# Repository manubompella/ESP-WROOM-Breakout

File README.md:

# ESP-WROOM-Breakout
Breakouts for ESP8266 and ESP32 WiFi/WLAN + Bluetooth modules from Espressif.
*Note: AI-Thinker ESP-13 is compatible with Espressif ESP-WROOM-02 and AI-Thinker ESP-32S is compatible with Espressif ESP-WROOM-32.*

## Shop
* [ESP-WROOM-02-Breakout (ESP8266)](http://www.watterott.com/en/ESP-WROOM02-Breakout)
* [ESP-WROOM-32-Breakout (ESP32)](http://www.watterott.com/en/ESP-WROOM32-Breakout)

## Features
* Espressif [ESP8266 ESP-WROOM-02](http://espressif.com/en/products/hardware/esp8266ex/overview) WiFi module
* Espressif [ESP32 ESP-WROOM-32](http://espressif.com/en/products/hardware/esp32/overview) WiFi+Bluetooth module
* WiFi standard: IEEE 802.11b/g/n 2.4GHz
* WiFi security: WEP, WPA, WPA2, WAPI
* WiFi Direct and Soft-AP (Access-Point mode)
* Classic and BLE Bluetooth (ESP32)
* Silabs [CP2102N](http://www.silabs.com/products/interface/usb-bridges/usbxpress-usb-bridges/Pages/usbxpress-usb-bridges.aspx) USB UART Bridge (up to 3M baud)
* microUSB-Connector

## Hardware and Software
* [Schematics + Layout](https://github.com/watterott/ESP-WROOM-Breakout/tree/master/hardware)
* ESP8266: [Arduino Core](https://github.com/esp8266/Arduino) (Board: NodeMCU v1)
* ESP32: [Arduino Core](https://github.com/espressif/arduino-esp32) (Board: ESP32 Dev Module)
* [Silabs Serial Port Driver (VCP)](http://www.silabs.com/products/mcu/pages/usbtouartbridgevcpdrivers.aspx)

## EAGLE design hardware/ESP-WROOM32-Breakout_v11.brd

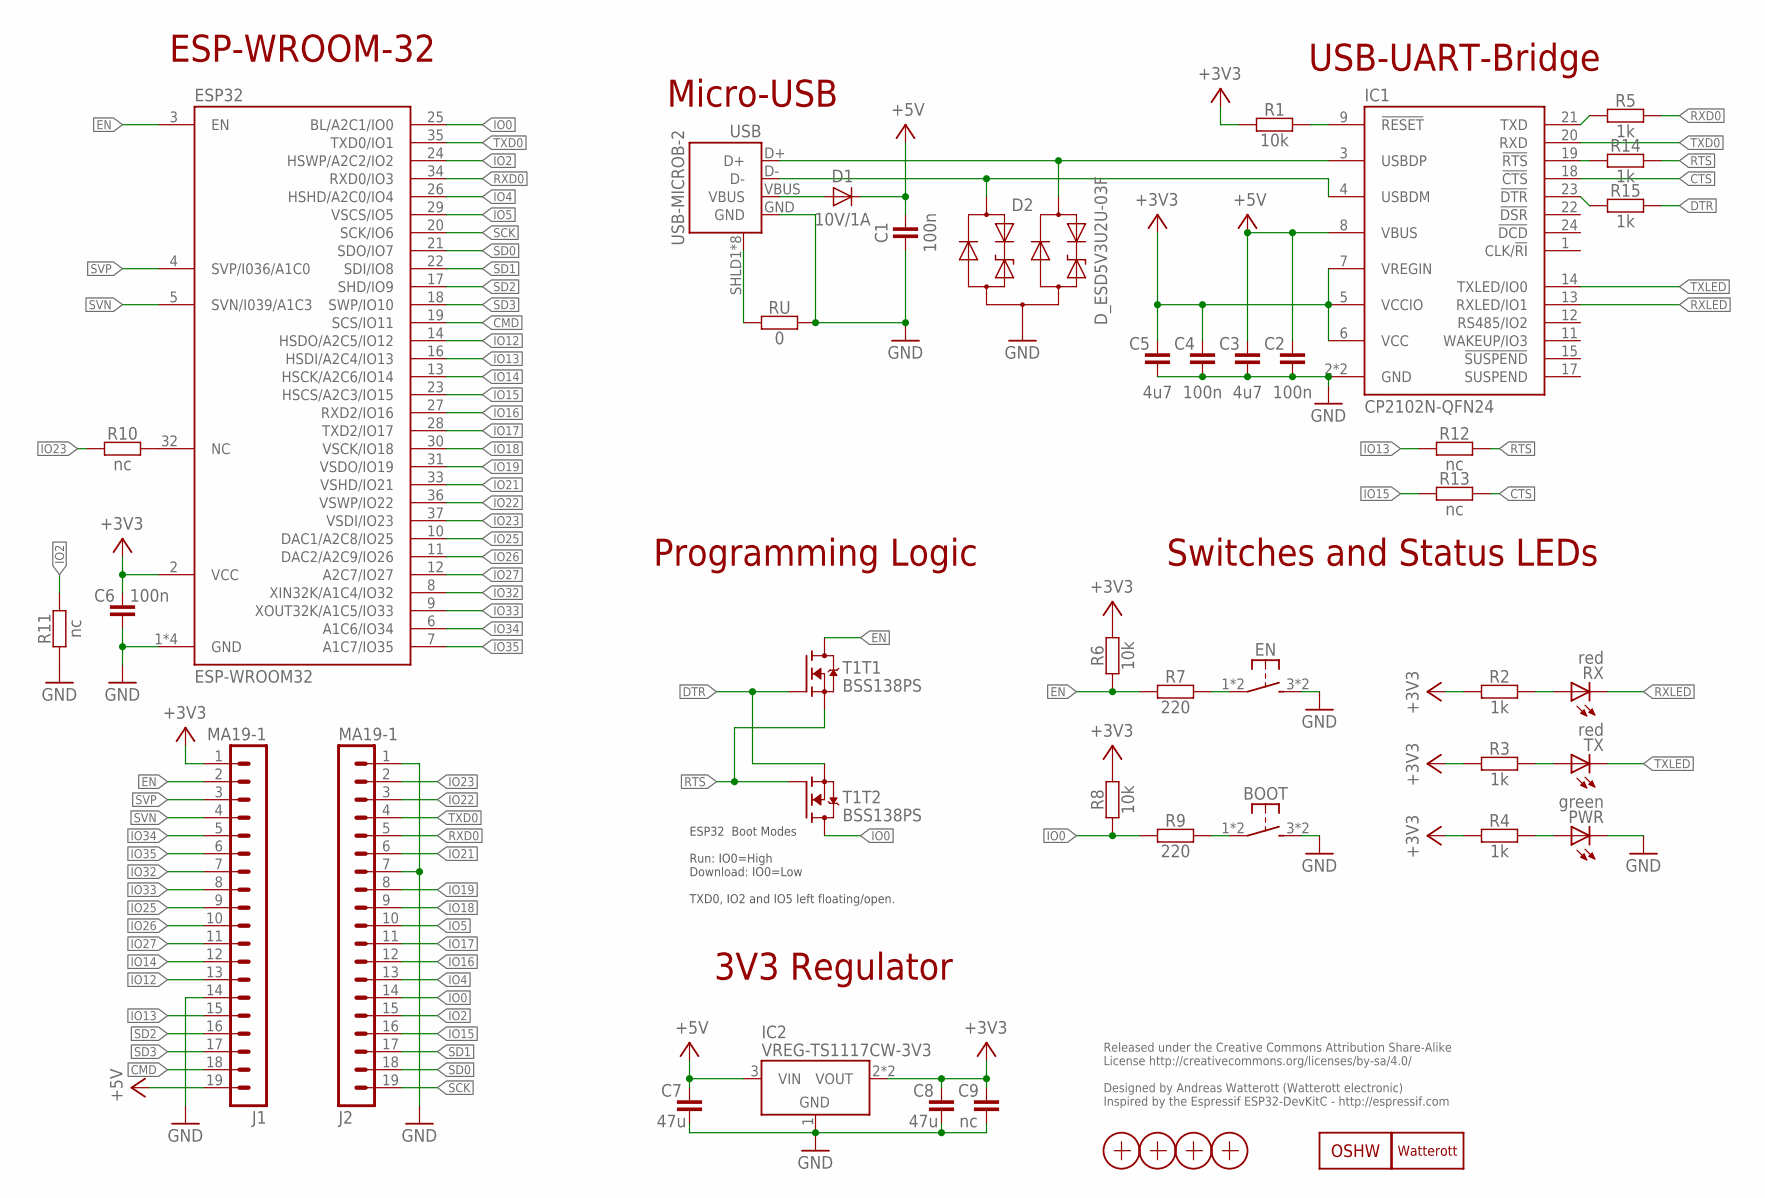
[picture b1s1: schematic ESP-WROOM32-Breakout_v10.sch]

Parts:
BOOT: SW-TACTILE-PTS840P; PTS840P
C1, C2, C4, C6: 100n; C0402
C3, C5: 4u7; C0603
C7, C8: 47u; C1206
C9: nc; C1206
D1: 10V/1A; SMA_DO214AC
D2: D_ESD5V3U2U-03F; SOT723
EN: SW-TACTILE-PTS840P; PTS840P
ESP32: ESP-WROOM32
IC1: CP2102N-QFN24; QFN24-PAD
IC2: VREG-TS1117CW-3V3; SOT223
J1, J2: MA19-1
LOGO2: OSHW_LOGOX0070; OSHW_6X70
LOGO4: LOGO-S_PLACE_M; SPARK_TPLACE_M
PWR: green; C0603
R1, R6, R8: 10k; C0402
R2, R3, R4, R5, R14, R15: 1k; C0402
R7, R9: 220; C0402
R10, R11, R12, R13: nc; C0402
RU: 0; C0402
RX: red; C0603
T1: BSS138PS; SOT363
TX: red; C0603
USB: USB-MICROB-2; USB-MICROB-10118194
X1, X2, X3, X4: PASSER-07; PASSER_07MM

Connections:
+3V3: C4.2, C5.2, C6.2, C8.2, C9.2, ESP32.2 (VCC), IC1.5 (VCCIO), IC1.6 (VCC), IC1.7 (VREGIN), IC2.2 (VOUT), IC2.4 (VOUT), J1.1, R1.1, R2.1, R3.1, R4.1, R6.2, R8.2
+5V: C1.2, C2.2, C3.2, C7.2, D1.C, IC1.8 (VBUS), IC2.3 (VIN), J1.19
CMD: ESP32.19 (SCS/IO11), J1.18
CPDTR: IC1.23 (!DTR), R15.1
CPRTS: IC1.19 (!RTS), R14.1
CPTX: IC1.21 (TXD), R5.1
CTS: IC1.18 (!CTS), R13.2
DTR: R15.2, T1.2 (G), T1.4 (S)
D_N: D2.1 (C1), IC1.4 (USBDM), USB.D-
D_P: D2.2 (C2), IC1.3 (USBDP), USB.D+
EN: ESP32.3 (EN), J1.2, R6.1, R7.1, T1.6 (D); also elsewhere on the board
GND: BOOT.3 (S1), BOOT.4 (S1), C1.1, C2.1, C3.1, C4.1, C5.1, C6.1, C7.1, C8.1, C9.1, D2.3 (A), EN.3 (S1), EN.4 (S1), ESP32.1 (GND), ESP32.15 (GND), ESP32.38 (GND), ESP32.TP (GND), IC1.2 (GND), IC1.TP (GND), IC2.1 (GND), J1.14, J2.1, J2.7, PWR.C, R11.1, RU.2, USB.GND; also elsewhere on the board
IO0: ESP32.25 (BL/A2C1/IO0), J2.14, R8.1, R9.1, T1.3 (D)
IO2: ESP32.24 (HSWP/A2C2/IO2), J2.15, R11.2
IO4: ESP32.26 (HSHD/A2C0/IO4), J2.13
IO5: ESP32.29 (VSCS/IO5), J2.10
IO12: ESP32.14 (HSDO/A2C5/IO12), J1.13
IO13: ESP32.16 (HSDI/A2C4/IO13), J1.15, R12.1
IO14: ESP32.13 (HSCK/A2C6/IO14), J1.12
IO15: ESP32.23 (HSCS/A2C3/IO15), J2.16, R13.1
IO16: ESP32.27 (RXD2/IO16), J2.12
IO17: ESP32.28 (TXD2/IO17), J2.11
IO18: ESP32.30 (VSCK/IO18), J2.9
IO19: ESP32.31 (VSDO/IO19), J2.8
IO21: ESP32.33 (VSHD/IO21), J2.6
IO22: ESP32.36 (VSWP/IO22), J2.3
IO23: ESP32.37 (VSDI/IO23), J2.2, R10.1
IO25: ESP32.10 (DAC1/A2C8/IO25), J1.9
IO26: ESP32.11 (DAC2/A2C9/IO26), J1.10
IO27: ESP32.12 (A2C7/IO27), J1.11
IO32: ESP32.8 (XIN32K/A1C4/IO32), J1.7
IO33: ESP32.9 (XOUT32K/A1C5/IO33), J1.8
IO34: ESP32.6 (A1C6/IO34), J1.5
IO35: ESP32.7 (A1C7/IO35), J1.6
unnamed: EN.1, EN.2 (P1), R7.2
unnamed: BOOT.1, BOOT.2 (P1), R9.2
NC: ESP32.32 (NC), R10.2
PWR-LED: PWR.A, R4.2
RESET: IC1.9 (!RESET), R1.2
RTS: R12.2, R14.2, T1.1 (S), T1.5 (G)
RX-LED: R2.2, RX.A
RXD0: ESP32.34 (RXD0/IO3), J2.5, R5.2
RXLED: IC1.13 (RXLED/IO1), RX.C
SCK: ESP32.20 (SCK/IO6), J2.19
SD0: ESP32.21 (SDO/IO7), J2.18
SD1: ESP32.22 (SDI/IO8), J2.17
SD2: ESP32.17 (SHD/IO9), J1.16
SD3: ESP32.18 (SWP/IO10), J1.17
SHLD: RU.1, USB.SHLD1 (SHIELD), USB.SHLD2 (SHIELD), USB.SHLD3 (SHIELD), USB.SHLD4 (SHIELD), USB.SHLD5 (SHIELD), USB.SHLD6 (SHIELD), USB.SHLD7 (SHIELD), USB.SHLD8 (SHIELD)
SVN: ESP32.5 (SVN/I039/A1C3), J1.4
SVP: ESP32.4 (SVP/I036/A1C0), J1.3
TX-LED: R3.2, TX.A
TXD0: ESP32.35 (TXD0/IO1), IC1.20 (RXD), J2.4
TXLED: IC1.14 (TXLED/IO0), TX.C
VBUS: D1.A, USB.VBUS

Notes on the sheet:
Released under the Creative Commons Attribution Share-Alike License http://creativecommons.org/licenses/by-sa/4.0/ Designed by Andreas Watterott (Watterott electronic) Inspired by the Espressif ESP32-DevKitC - http://espressif.com
USB-UART-Bridge
Micro-USB
Switches and Status LEDs
Programming Logic
ESP-WROOM-32
3V3 Regulator
ESP32 Boot Modes Run: IO0=High Download: IO0=Low TXD0, IO2 and IO5 left floating/open.

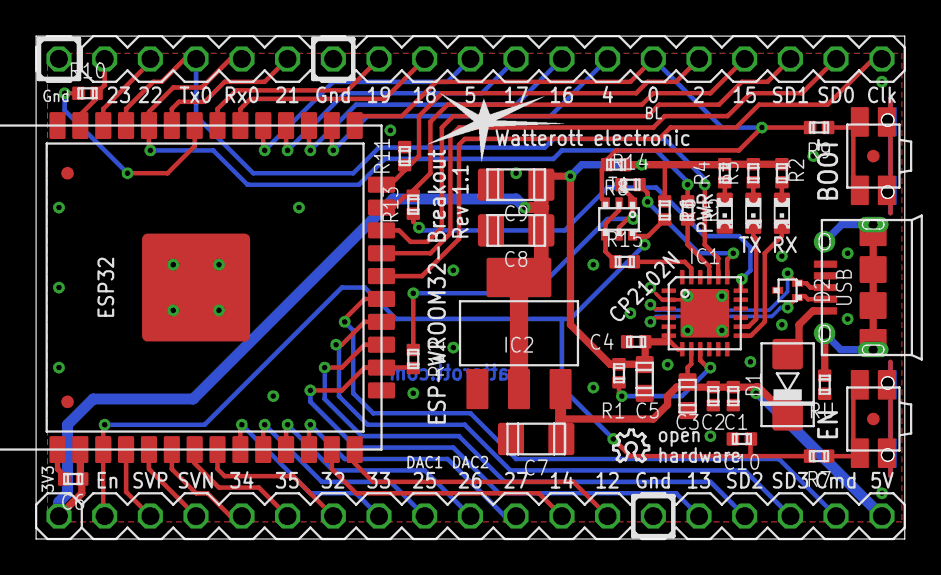
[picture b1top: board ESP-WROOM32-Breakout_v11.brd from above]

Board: 2 copper layers, 48.3 x 27.9 mm, 46 parts (0 on the bottom side), 55 nets.

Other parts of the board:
C10: 2u2; C0402

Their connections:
EN: C10.2; also elsewhere on the board
GND: C10.1; also elsewhere on the board

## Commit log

2016-10-23 added readme
2016-11-06 added layout and schematics
2016-11-08 updated schematics
2016-11-16 added rev 1.1
2016-11-18 updated images
